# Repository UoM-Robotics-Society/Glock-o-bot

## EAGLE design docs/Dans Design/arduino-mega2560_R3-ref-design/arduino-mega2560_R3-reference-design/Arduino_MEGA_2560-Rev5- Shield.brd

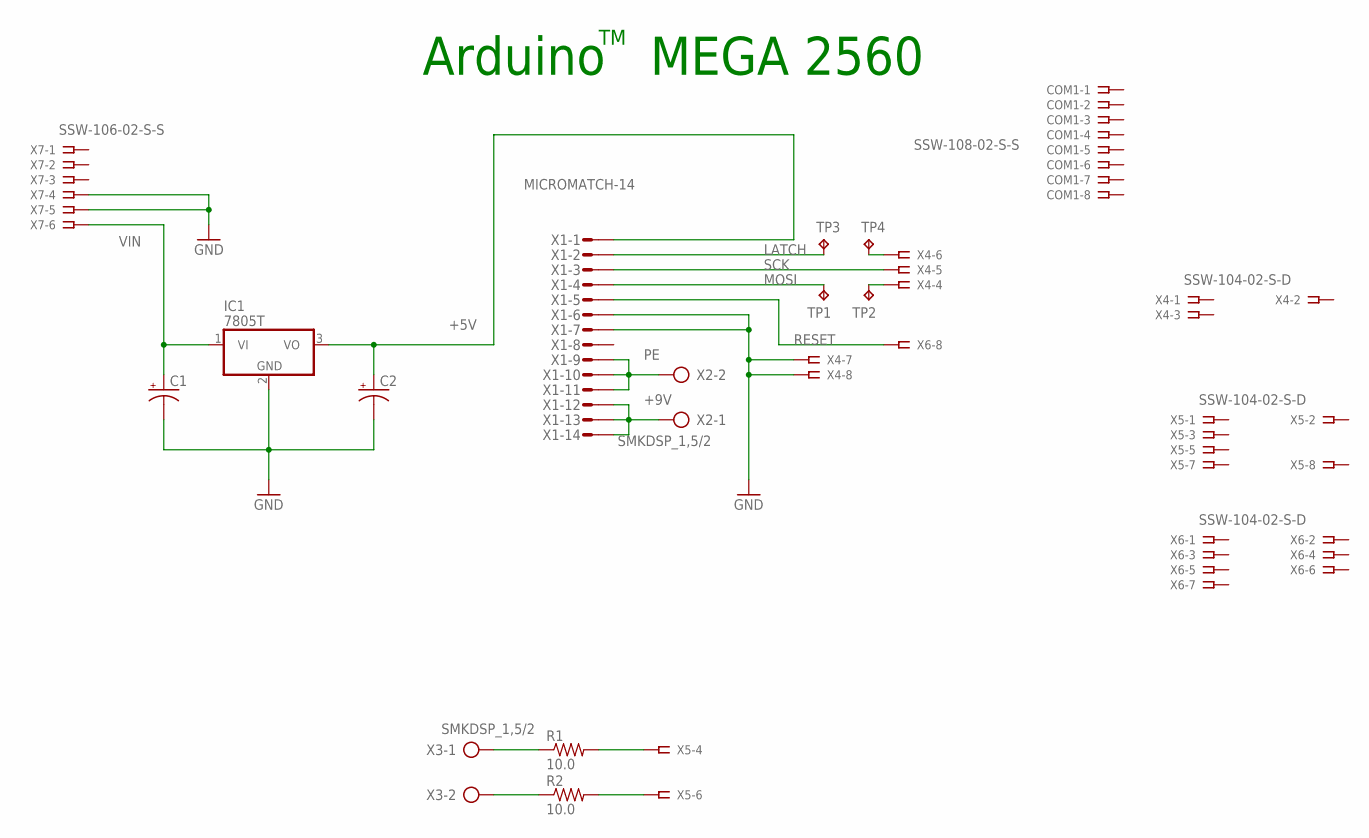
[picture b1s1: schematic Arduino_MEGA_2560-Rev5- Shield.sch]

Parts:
C1, C2: CAP_POL7343; EIA7343
COM1: SSW-108-02-S-S
IC1: 7805T; TO220H
R1, R2: 10.0; AXIAL-0.1
TP1, TP2, TP3, TP4: TPPAD1-13; P1-13
X1: MICROMATCH-14
X2, X3: SMKDSP_1,5/2
X4, X5, X6: SSW-104-02-S-D
X7: SSW-106-02-S-S

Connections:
+5V: C2.A (+), IC1.3 (VO), X1.1
+9V: X1.12, X1.13, X1.14, X2.1
GND: C1.C (-), C2.C (-), IC1.2 (GND), X1.6, X1.7, X4.7, X4.8, X7.4, X7.5
LATCH: TP3.TP, X1.2
MOSI: TP1.TP, X1.4
unnamed: R1.P$1 (1), X3.1
unnamed: R1.P$2 (2), X5.4
unnamed: R2.P$1 (1), X3.2
unnamed: R2.P$2 (2), X5.6
unnamed: TP2.TP, X4.4
unnamed: TP4.TP, X4.6
PE: X1.9, X1.10, X1.11, X2.2
RESET: X1.5, X6.8
SCK: X1.3, X4.5
VIN: C1.A (+), IC1.1 (VI), X7.6

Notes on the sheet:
Arduino MEGA 2560

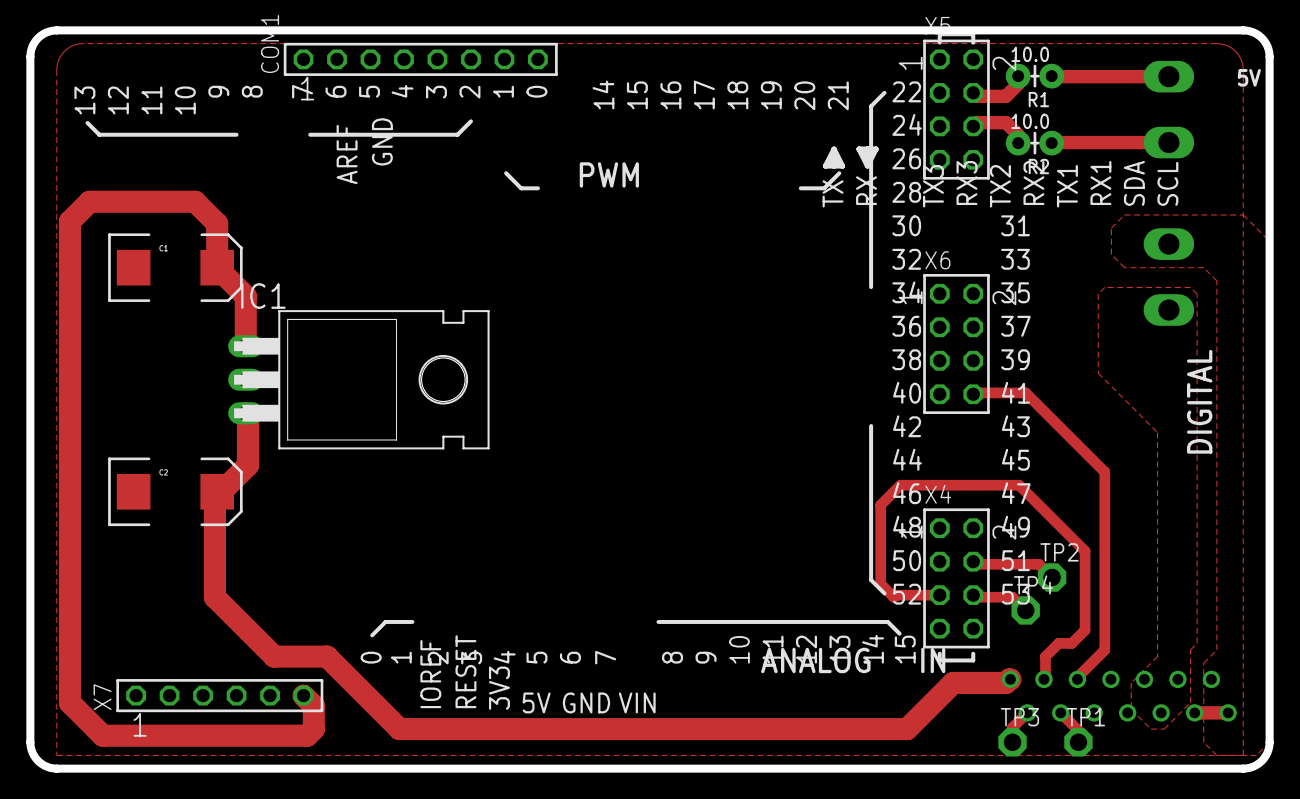
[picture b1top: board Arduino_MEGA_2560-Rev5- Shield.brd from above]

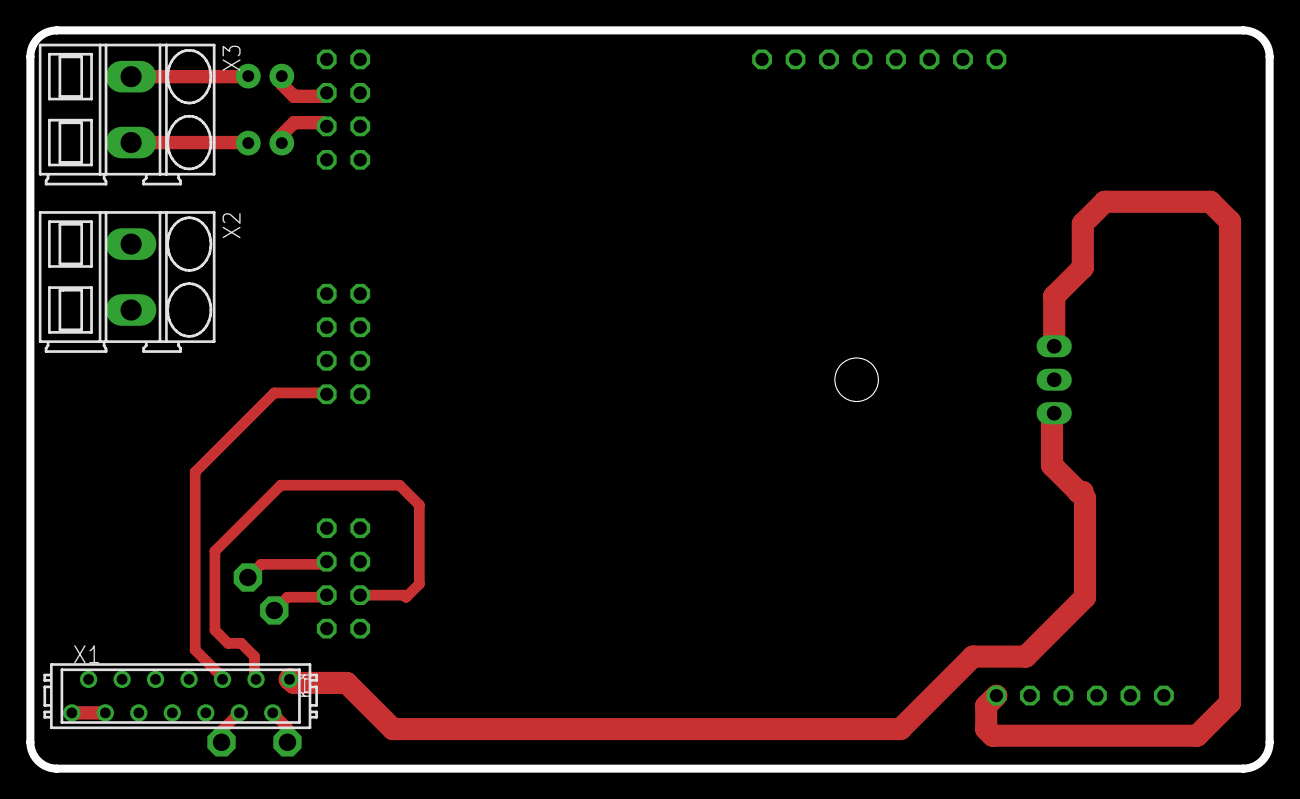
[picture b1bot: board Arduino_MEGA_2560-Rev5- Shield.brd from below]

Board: 2 copper layers, 94.0 x 56.0 mm, 17 parts (3 on the bottom side), 15 nets.

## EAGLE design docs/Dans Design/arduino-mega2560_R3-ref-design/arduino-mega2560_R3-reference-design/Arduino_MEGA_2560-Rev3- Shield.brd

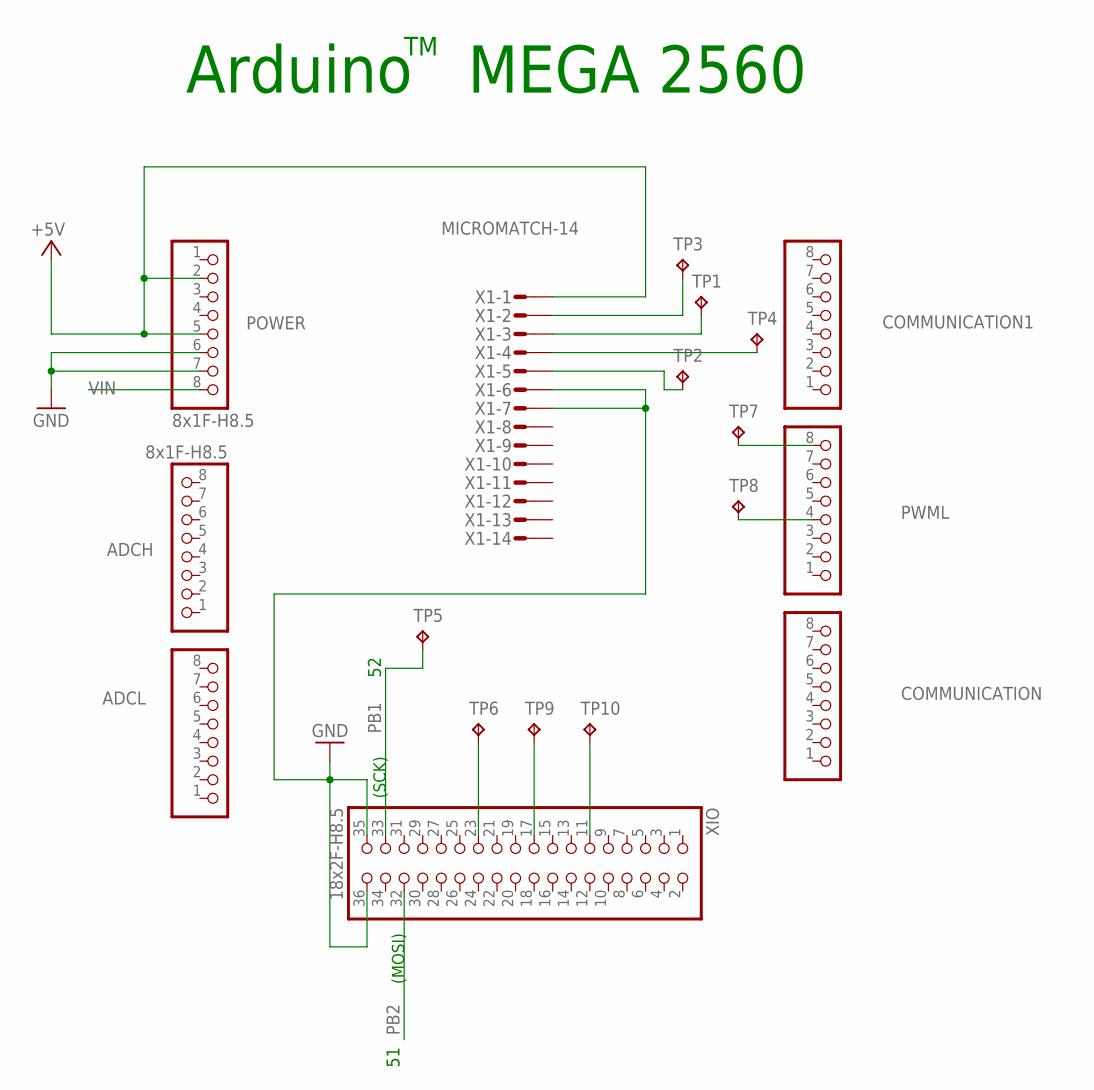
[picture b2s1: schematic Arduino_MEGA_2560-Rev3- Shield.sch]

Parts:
ADCH: 8x1F-H8.5; 1X08
ADCL: 8x1F-H8.5; 1X08
COMMUNICATION, COMMUNICATION1: 8x1F-H8.5; 1X08
POWER: 8x1F-H8.5; 1X08
PWML: 8x1F-H8.5; 1X08
TP1, TP2, TP3, TP4, TP5, TP6, TP7, TP8, TP9, TP10: TPPAD1-13; P1-13
X1: MICROMATCH-14
XIO: 18x2F-H8.5; 2X18

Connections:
+5V: POWER.2, POWER.5, X1.1
GND: POWER.6, POWER.7, X1.6, X1.7, XIO.35, XIO.36
unnamed: TP1.TP, X1.3
unnamed: TP4.TP, X1.4
unnamed: TP3.TP, X1.2
unnamed: TP2.TP, X1.5
unnamed: PWML.8, TP7.TP
unnamed: PWML.4, TP8.TP
unnamed: TP6.TP, XIO.23
unnamed: TP9.TP, XIO.17
unnamed: TP10.TP, XIO.11
PB1: TP5.TP, XIO.33
PB2: XIO.32
VIN: POWER.8

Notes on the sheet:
Arduino MEGA 2560
(MOSI)
(SCK)

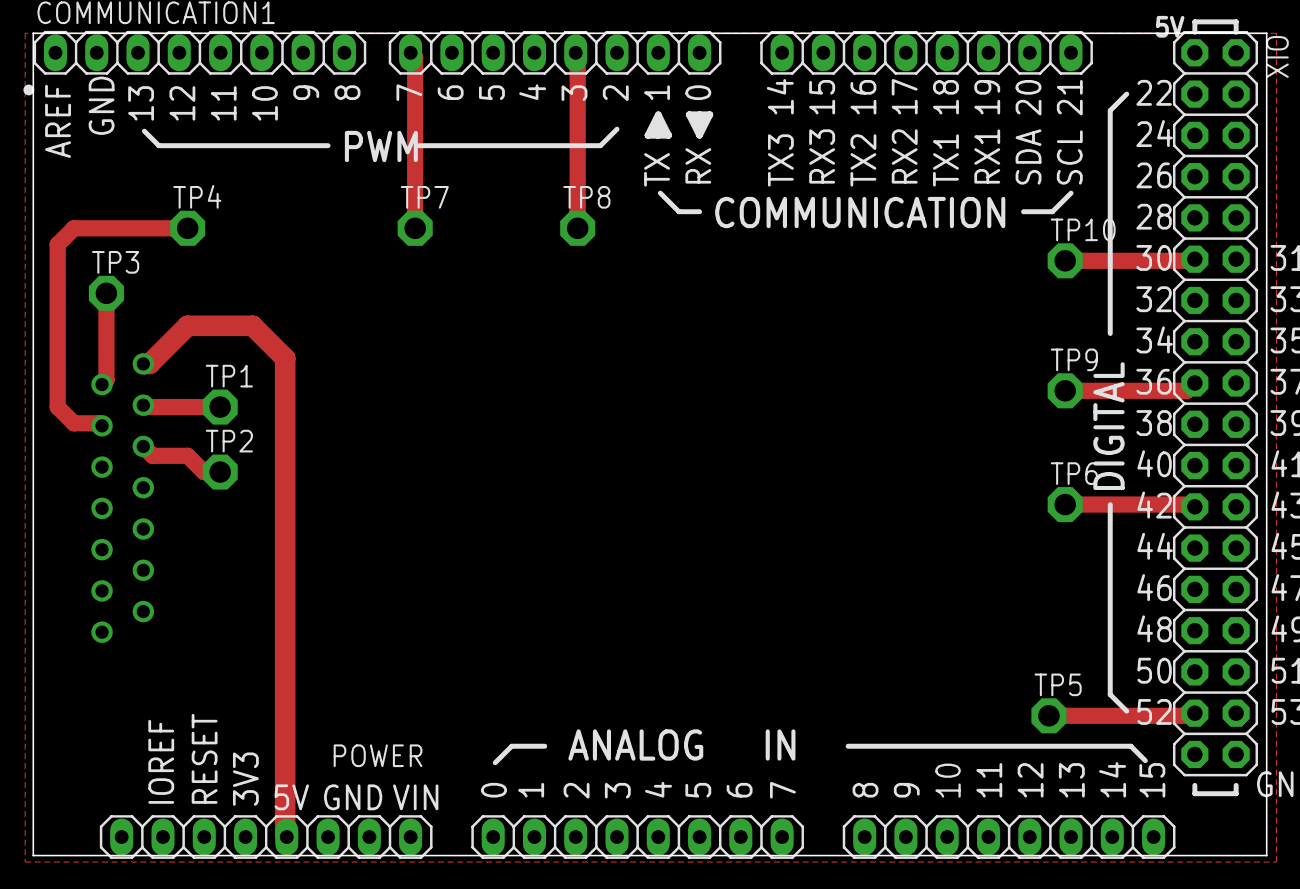
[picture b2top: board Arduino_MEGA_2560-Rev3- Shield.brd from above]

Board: 2 copper layers, 75.9 x 50.6 mm, 18 parts (1 on the bottom side), 12 nets.

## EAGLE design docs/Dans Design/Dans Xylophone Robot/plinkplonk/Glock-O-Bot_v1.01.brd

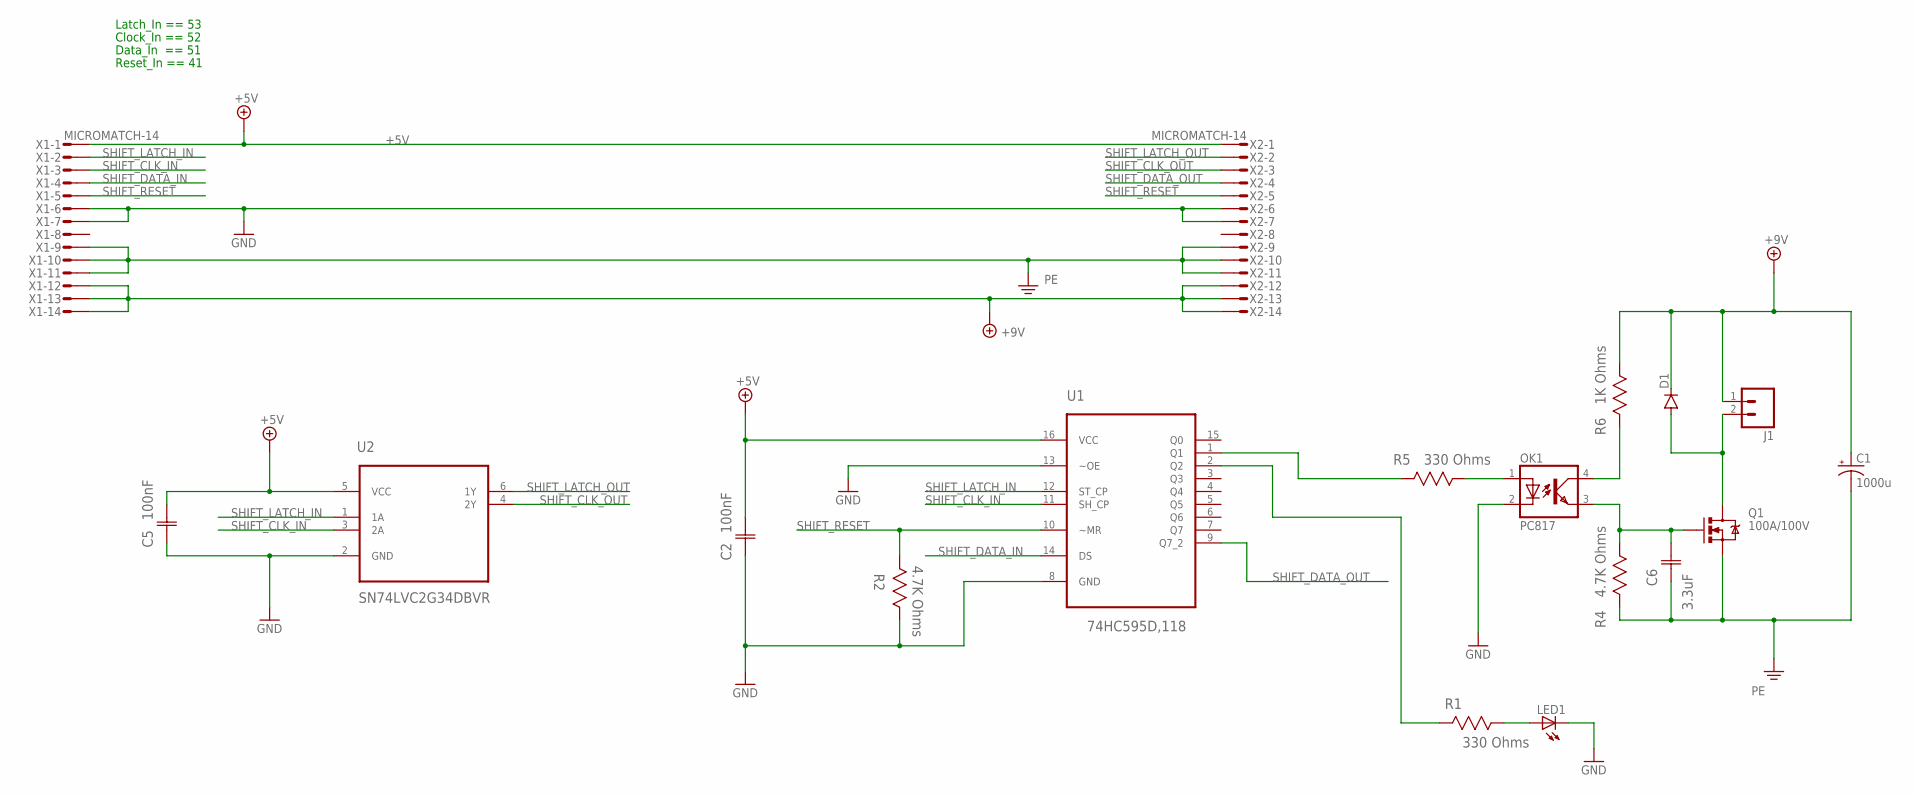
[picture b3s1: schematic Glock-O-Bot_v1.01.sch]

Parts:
C1: 1000u; CPOL-RADIAL-1000UF-25V; FARNELL 9693610
C2, C5: 100nF; CAPC2013X110N; FARNELL 1414663
C6: 3.3uF; CAPC2013X110N; VOLTAGERATING 16V; FARNELL 1572630
D1: DIODEPTH; DIODE-1N4001; FARNELL 9564993
J1: M02JST-PTH-VERT; JST-2-PTH-VERT
LED1: LEDCHIPLED_1206; CHIPLED_1206; FARNELL 8530076
OK1: PC817; DIL04; MPN FOD817A; FARNELL 2322514
Q1: 100A/100V; TO-263/D2PAK; FARNELL 2254193
R1, R5: 330 Ohms; RESC2013X65N; FARNELL 2073741
R2, R4: 4.7K Ohms; RESC2013X65N; FARNELL 9333266
R6: 1K Ohms; RESC2013X65N; FARNELL 2073606
U1: 74HC595D,118; SOIC127P600X175-16N; FARNELL 1201269
U2: SN74LVC2G34DBVR; SOT95P280X145-6N; FARNELL 1470888
X1, X2: MICROMATCH-14

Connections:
+5V: C2.2 (C2), C5.2 (C2), U1.16 (VCC), U2.5 (VCC), X1.1, X2.1
+9V: C1.+, D1.C, J1.1, R6.1 (R1), X1.12, X1.13, X1.14, X2.12, X2.13, X2.14
GND: C2.1 (C1), C5.1 (C1), LED1.C, OK1.2 (C), R2.1 (R1), U1.8 (GND), U1.13 (~OE), U2.2 (GND), X1.6, X1.7, X2.6, X2.7
unnamed: D1.A, J1.2, Q1.2 (D)
unnamed: R1.2 (R2), U1.2 (Q2)
unnamed: C6.2 (C2), OK1.3 (EMIT), Q1.1 (G), R4.1 (R1)
unnamed: LED1.A, R1.1 (R1)
unnamed: OK1.4 (COL), R6.2 (R2)
unnamed: R5.2 (R2), U1.1 (Q1)
unnamed: OK1.1 (A), R5.1 (R1)
PE: C1.-, C6.1 (C1), Q1.3 (S), R4.2 (R2), X1.9, X1.10, X1.11, X2.9, X2.10, X2.11
SHIFT_CLK_IN: U1.11 (SH_CP), U2.3 (2A), X1.3
SHIFT_CLK_OUT: U2.4 (2Y), X2.3
SHIFT_DATA_IN: U1.14 (DS), X1.4
SHIFT_DATA_OUT: U1.9 (Q7_2), X2.4
SHIFT_LATCH_IN: U1.12 (ST_CP), U2.1 (1A), X1.2
SHIFT_LATCH_OUT: U2.6 (1Y), X2.2
SHIFT_RESET: R2.2 (R2), U1.10 (~MR), X1.5, X2.5

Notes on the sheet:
Latch_In == 53
Clock_In == 52
Data_In == 51
Reset_In == 41

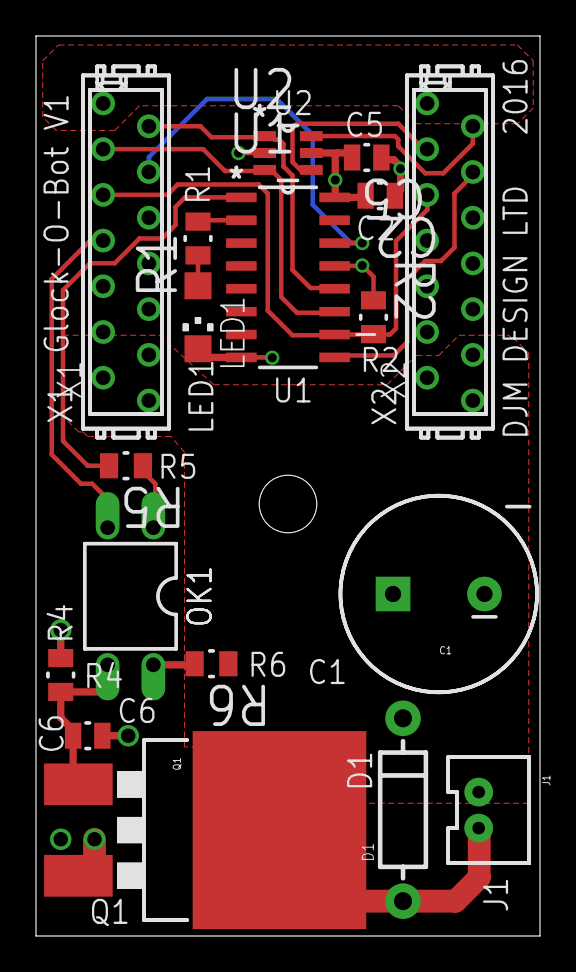
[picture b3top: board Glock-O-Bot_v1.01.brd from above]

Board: 2 copper layers, 28.0 x 50.0 mm, 18 parts (0 on the bottom side), 18 nets.

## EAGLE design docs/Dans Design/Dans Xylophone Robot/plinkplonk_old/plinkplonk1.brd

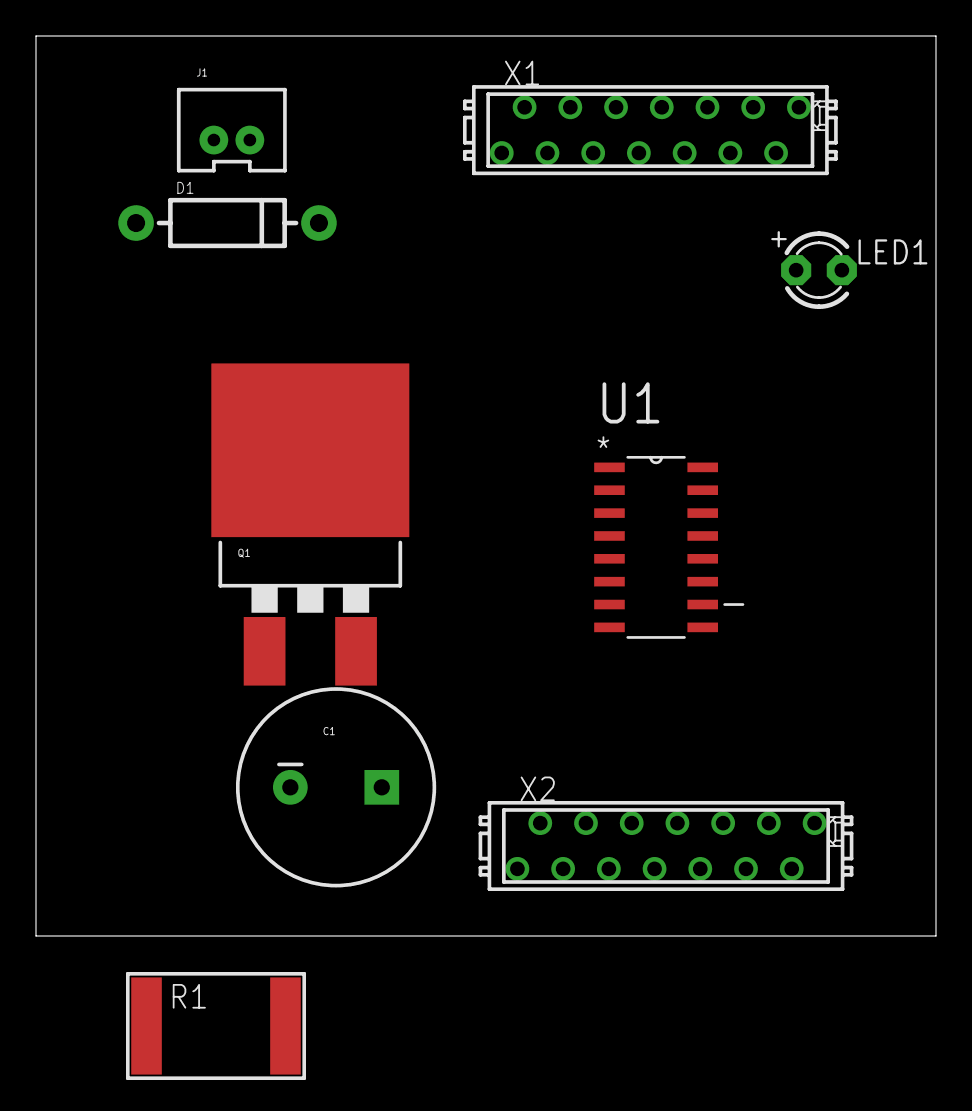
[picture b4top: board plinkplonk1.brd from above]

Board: 2 copper layers, 50.0 x 50.0 mm, 9 parts (0 on the bottom side), 4 nets, no tracks yet.

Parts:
C1: CPOL-RADIAL-1000UF-25V
D1: DIODE-1N4001
J1: JST-2-PTH-VERT
LED1: LED3MM
Q1: 100A/100V; TO-263/D2PAK
R1: PMD
U1: 74HC595D,118; SOIC127P600X175-16N
X1, X2: MICROMATCH-14

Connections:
unnamed: D1.A, J1.2, Q1.2
unnamed: D1.C, J1.1
unnamed: C1.+, Q1.1
unnamed: C1.-, Q1.3

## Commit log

2022-08-24 Initial commit
    Upload of legacy files provided by Will

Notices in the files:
parts and their libraries:
SparkFun-Capacitors: Licensing: Creative Commons ShareAlike 4.0 International - https://creativecommons.org/licenses/by-sa/4.0
